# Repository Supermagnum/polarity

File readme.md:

This PCB board is 31mm in diameter, it has a single P-Channel IRLR9343TRPBF mosfet that is capable of tolerating 20V 20A. 
It should be fairly simple to solder, even that it is surface mounted. 

It does not conduct any electricity if subjected to the wrong polarity. 

It has two 11mm solder pads,the one on the DC+ OUT protected side can be soldered to the top of your existing drivers spring,or a wire. 
There is also a DC- or ground connection solder connection or a outer circular connection that is suitable for a snap ring or compression connection, 
I suggest a AVG 15 (1.45 mm diameter ) flexible wire for a solder connetion. 
The DC+ unprotected side goes to the batteries. It is possible to solder a spring there if needed.

The PCB is here:

https://oshpark.com/shared_projects/WsPtYNPE

PCB + part:

https://aisler.net/p/LPKPSYXG

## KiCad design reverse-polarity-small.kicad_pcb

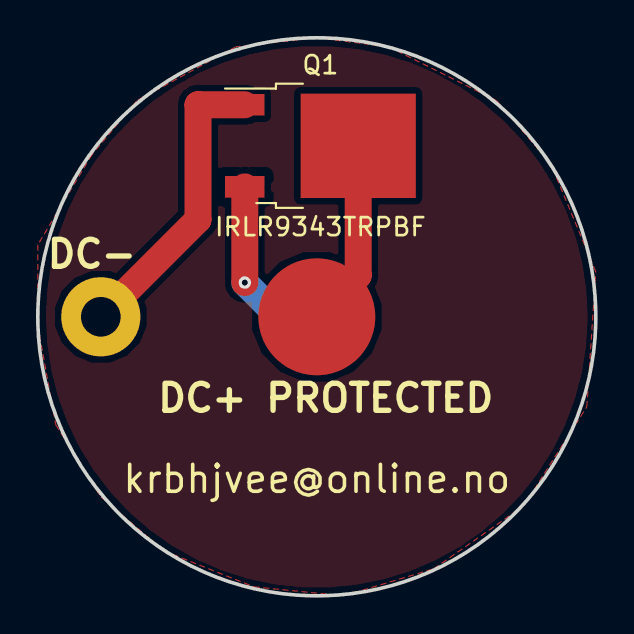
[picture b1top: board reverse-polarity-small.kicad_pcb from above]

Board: 2 copper layers, 31.0 x 31.0 mm, 4 parts (0 on the bottom side), 2 nets.

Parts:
J1, J2, J3: 105-1102-001; MountingHole_2.2mm_M2_Pad
Q1: IRLR9343TRPBF; TO-252-3_TabPin4

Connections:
/DC+prot: J3.1, Q1.4
/GND: J2.1, Q1.1

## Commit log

2020-08-14 Updates
    Added a outer circle that is connected to DC-.
2020-08-14 Add files via upload
    Added a outer circle that is connected to DC-
2020-08-14 created readme.md
2020-08-14 Add files via upload
    uploaded gerber and drill files.
2020-08-15 updated, now fits 31mmØ holder or tube
